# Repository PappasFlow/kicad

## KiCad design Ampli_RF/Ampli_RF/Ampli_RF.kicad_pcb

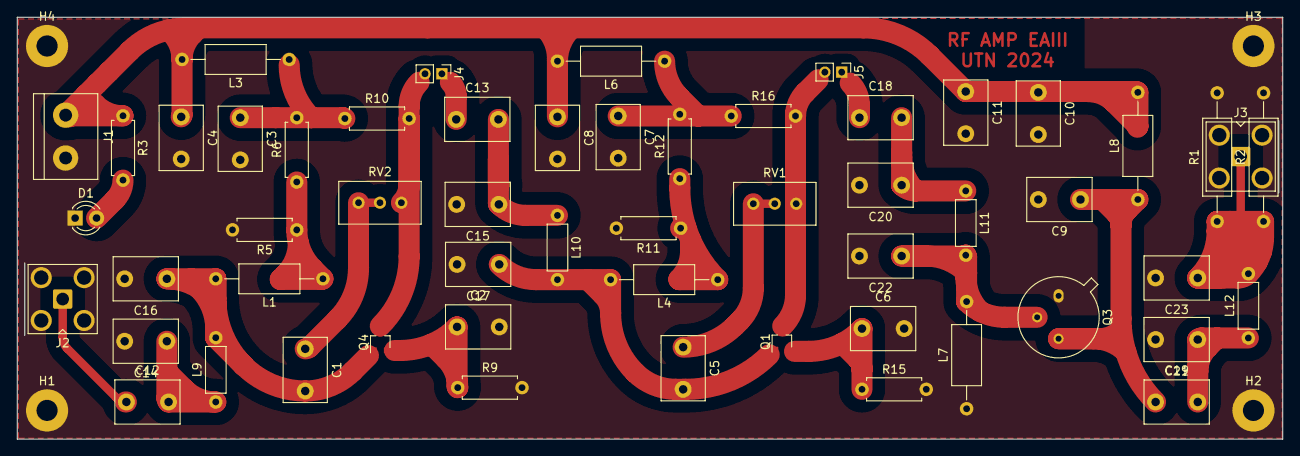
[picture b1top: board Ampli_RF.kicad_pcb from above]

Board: 2 copper layers, 150.0 x 50.0 mm, 59 parts (0 on the bottom side), 25 nets.

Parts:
C1, C2, C3, C4, C5, C6, C7, C8, C9, C10, C11, C12, C13, C14, C15, C16, C17, C18, C19, C20, C21, C22, C23: C; C_Disc_D7.5mm_W5.0mm_P5.00mm
D1: LED; LED_D3.0mm
H1, H2, H3, H4: MountingHole_Pad; MountingHole_2.5mm_Pad
J1: Con_power; TerminalBlock_bornier-2_P5.08mm
J2, J3: Con_signal; SMA_Amphenol_901-143_Horizontal
J4: E1; PinHeader_1x02_P2.00mm_Vertical
J5: E2; PinHeader_1x02_P2.00mm_Vertical
L1, L3, L4, L6, L7, L8: L; L_Axial_L7.0mm_D3.3mm_P12.70mm_Horizontal_Fastron_MICC
L9, L10, L11, L12: L; L_Axial_L5.3mm_D2.2mm_P7.62mm_Horizontal_Vishay_IM-1
Q1: BFR106; SOT-323_SC-70
Q3: 2N2219; TO-39-3
Q4: BFR182; SOT-323_SC-70
R1, R2: R; R_Axial_DIN0309_L9.0mm_D3.2mm_P15.24mm_Horizontal
R3, R5, R6, R9, R10, R11, R12, R15, R16: R; R_Axial_DIN0207_L6.3mm_D2.5mm_P7.62mm_Horizontal
RV1, RV2: pot; Potentiometer_Bourns_3296W_Vertical

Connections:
2N3866_in: C22.1, L7.2, L11.2, Q3.2 (B)
2N3866_out: C9.1, C19.1, L8.1, Q3.3 (C)
+12V: C4.1, C8.1, C10.1, C11.1, J1.1, L3.2, L6.2, L8.2, R3.1
BFR106_in: C5.2, C17.1, L4.2, L10.2, Q1.1 (B)
BFR106_out: J5.2, Q1.3 (C), R16.2, RV1.1
BFR182_in: C1.2, C16.1, L1.2, L9.2, Q4.1 (B)
BFR182_out: J4.2, Q4.3 (C), R10.2, RV2.1
GND: C2.2, C3.2, C4.2, C6.2, C7.2, C8.2, C9.2, C10.2, C11.2, C14.2, C15.2, C16.2, C17.2, C20.2, C21.2, C22.2, C23.2, D1.1 (K), H1.1, H2.1, H3.1, H4.1, J1.2, J2.2, J3.2, L7.1, Q3.1 (E), R1.2, R2.2, R5.2, R9.2, R11.2, R15.2
unnamed: C1.1, RV2.2, RV2.3
unnamed: C3.1, L3.1, R6.2, R10.1
unnamed: C5.1, RV1.2, RV1.3
unnamed: C7.1, L6.1, R12.2, R16.1
unnamed: C12.2, C14.1, L9.1
unnamed: C13.2, C15.1, L10.1
unnamed: C18.2, C20.1, L11.1
unnamed: C19.2, C21.1, L12.1
unnamed: D1.2 (A), R3.2
unnamed: C13.1, J4.1
unnamed: C18.1, J5.1
unnamed: L1.1, R5.1, R6.1
unnamed: L4.1, R11.1, R12.1
unnamed: C6.1, Q1.2 (E), R15.1
unnamed: C2.1, Q4.2 (E), R9.1
Output: C23.1, J3.1, L12.2, R1.1, R2.1
input: C12.1, J2.1

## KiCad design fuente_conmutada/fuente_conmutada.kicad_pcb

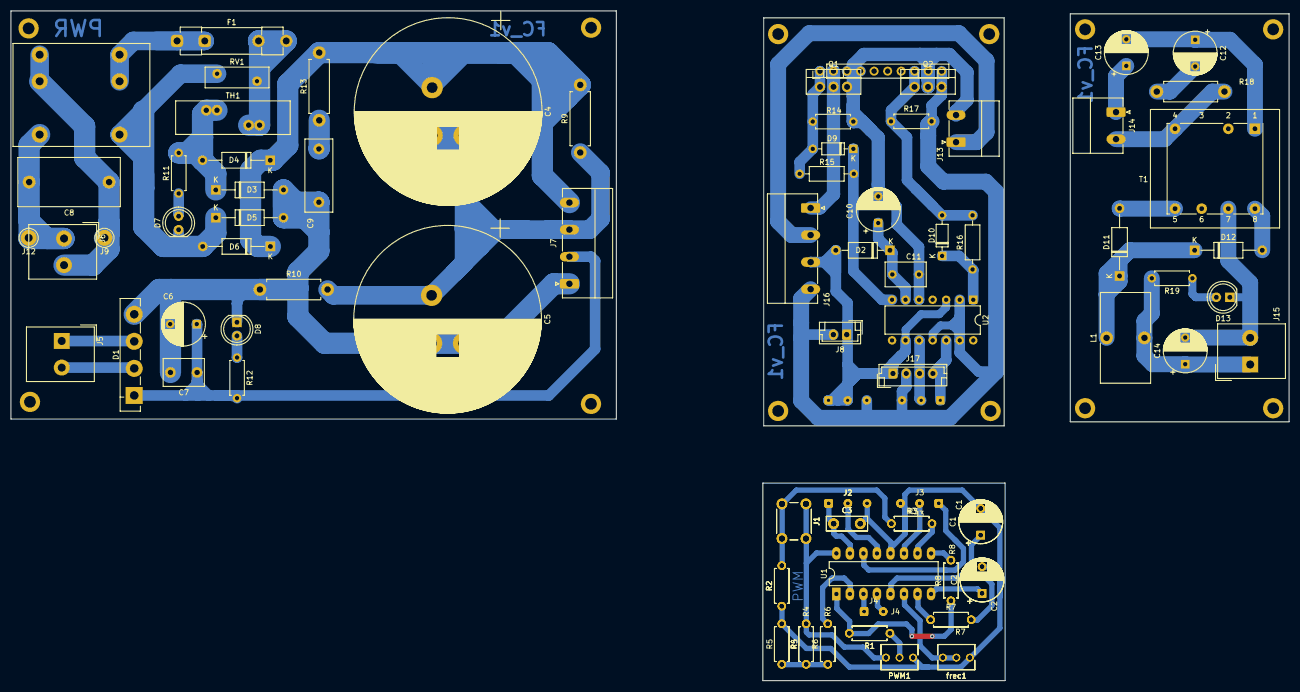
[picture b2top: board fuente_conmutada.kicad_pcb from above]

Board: 2 copper layers, 239.9 x 125.7 mm, 105 parts (0 on the bottom side), 46 nets.

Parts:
C1, C1#2: 1nF; CP_Radial_D8.0mm_P5.00mm
C2, C2#2: 10uF; CP_Radial_D8.0mm_P5.00mm
C3, C3#2: 0.1uF; C_Disc_D7.5mm_W2.5mm_P5.00mm
C4, C5: 470u; CP_Radial_D35.0mm_P9mm
C6: 1000uF; CP_Radial_D8.0mm_P5.00mm
C7: 100nF; C_Disc_D7.5mm_W5.0mm_P5.00mm
C8: 47n; C_Rect_L19.0mm_W9.0mm_P15.00mm_MKS4
C9: 10n; C_Rect_L13.5mm_W5.0mm_P10.00mm_FKS3_FKP3_MKS4
C10, C12, C13, C14: 100n; CP_Radial_D8.0mm_P5.00mm
C11: 22u; C_Disc_D7.5mm_W4.4mm_P5.00mm
D1: D_Bridge_+-AA; Diode_Bridge_Vishay_GBL
D2: D; D_A-405_P10.16mm_Horizontal
D3, D4, D5, D6, D11, D12: D; D_A-405_P12.70mm_Horizontal
D7, D8, D13: LED; LED_D5.0mm
D9, D10: 1N4148; D_DO-35_SOD27_P7.62mm_Horizontal
F1: Fuse; Fuseholder_Clip-5x20mm_Littelfuse_445-030_Inline_P20.50x5.2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
FL1: Filter_EMI; L_CommonMode_Toroid_filter_emi
H1, H2, H3, H4, H5, H6, H7, H8, H9, H10, H11, H12: MountingHole; MountingHole_2.2mm_M2_DIN965_Pad
J1, J1#2: shutdown; SW_PUSH_6mm_H9.5mm
J2, J2#2, J3, J3#2: Conn_01x03; SolderWire-0.1sqmm_1x03_P3.6mm_D0.4mm_OD1mm
J4, J4#2: Conn_01x02; SolderWire-0.1sqmm_1x02_P3.6mm_D0.4mm_OD1mm
J5: 12v _in; Altech_AK300_1x02_P5.00mm_45-Degree
J6: in_red; Altech_AK300_1x02_P5.00mm_45-Degree
J7: out_pwr; PhoenixContact_MC_1,5_4-G-5.08_1x04_P5.08mm_Horizontal
J8: fan; JST_EH_B2B-EH-A_1x02_P2.50mm_Vertical
J9, J12: pin; Pin_D1.3mm_L11.0mm_LooseFit
J10: pwm_power; SolderWire-0.1sqmm_1x03_P3.6mm_D0.4mm_OD1mm
J11: pwm_señal; SolderWire-0.1sqmm_1x03_P3.6mm_D0.4mm_OD1mm
J13: trafo; PhoenixContact_MC_1,5_2-G-5.08_1x02_P5.08mm_Horizontal
J14: in_trafo; PhoenixContact_MC_1,5_2-G-5.08_1x02_P5.08mm_Horizontal
J15: out_R; Altech_AK300_1x02_P5.00mm_45-Degree
J16: in_pwr; PhoenixContact_MC_1,5_4-G-5.08_1x04_P5.08mm_Horizontal
J17: in_pwr; JST_EH_B4B-EH-A_1x04_P2.50mm_Vertical
J19: montage; PinHeader_1x10_P2.54mm_Vertical
L1: L; L_Toroid_Vertical_L16.8mm_W9.2mm_P7.10mm_Vishay_TJ3
PWM1, PWM1#2: 10k; Potentiometer_Bourns_3266Y_Vertical
Q1, Q2: IRF740; TO-220-3_Vertical
R1, R1#2, R6, R6#2, R8, R8#2, R12: 1k; R_Axial_DIN0207_L6.3mm_D2.5mm_P7.62mm_Horizontal
R2, R2#2, R3, R3#2: 5k; R_Axial_DIN0207_L6.3mm_D2.5mm_P7.62mm_Horizontal
R4, R4#2, R5, R5#2, R14, R17: 10k; R_Axial_DIN0207_L6.3mm_D2.5mm_P7.62mm_Horizontal
R7, R7#2: 330; R_Axial_DIN0207_L6.3mm_D2.5mm_P7.62mm_Horizontal
R9, R10, R18: 150k; R_Axial_DIN0411_L9.9mm_D3.6mm_P12.70mm_Horizontal
R11, R19: 22k; R_Axial_DIN0207_L6.3mm_D2.5mm_P7.62mm_Horizontal
R13: 100; R_Axial_DIN0411_L9.9mm_D3.6mm_P12.70mm_Horizontal
R15, R16: 100; R_Axial_DIN0207_L6.3mm_D2.5mm_P10.16mm_Horizontal
RV1: Varistor; RV_Disc_D12mm_W3.9mm_P7.5mm
T1: Transformer_1P_SS; Transformer_Breve_TEZ-22x24
TH1: NTC; RV_Disc_D21.5mm_W6.3mm_P10mm
U1: UC3525; DIP-16_W7.62mm_LongPads
U2: IR2110; DIP-14_W7.62mm
frec1, frec1#2: 150k; Potentiometer_Bourns_3266Y_Vertical

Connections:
1a: D9.2 (A), J19.1, Q1.1 (G), R14.1, R15.2
1b: D10.2 (A), J19.8, Q2.1 (G), R16.2, R17.1
155V: C4.2, C5.1, J7.3, J13.1, J14.2, J16.2, R9.1, R10.2, R18.1, T1.2 (AB)
310V: C4.1, D4.1 (K), D6.1 (K), J7.4, J16.1, J19.2, Q1.2 (D), R9.2, R13.2
+12V: C3.1, J2.1
Fase: D3.1 (K), D4.2 (A), R11.2, TH1.2
GND: C1.2, C1#2.2, C2.2, C2#2.2, C3.2, C3#2.2, C5.2, C6.2, C7.2, C9.2, D1.4 (-), D3.2 (A), D5.2 (A), D8.1 (K), J2.3, J2#2.3, J3.3, J3#2.3, J7.1, J8.2, J10.3, J11.3, J16.4, J17.2, J19.10, PWM1.3, PWM1#2.3, Q2.3 (S), R2.1, R2#2.1, R5.1, R5#2.1, R10.1, R17.2, U1.12 (GND), U2.2 (COM), U2.11 (SD), U2.13 (VSS), frec1.3, frec1#2.3
GNDREF: C14.2, D13.1 (K), J15.2, T1.4 (SC)
HO: D9.1 (K), R15.1, U2.7 (HO)
LO: D10.1 (K), R16.1, U2.1 (LO)
unnamed: C9.1, R13.1
unnamed: C12.2, R18.2
unnamed: C10.1, C11.1, D2.1 (K), U2.6 (VB)
unnamed: D7.2 (A), R11.1
unnamed: D8.2 (A), R12.1
unnamed: D11.2 (A), T1.5 (SB)
unnamed: D11.1 (K), D12.1 (K), L1.1
unnamed: D12.2 (A), T1.3 (SA)
unnamed: D13.2 (A), R19.1
unnamed: F1.1, FL1.2
unnamed: F1.2, RV1.1, TH1.1
unnamed: J1.2, J1#2.2, R2.2, R2#2.2, R3.1, R3#2.1
unnamed: D1.3, J5.1
unnamed: D1.2, J5.2
unnamed: C8.1, FL1.1, J6.2, J9.1
unnamed: C8.2, FL1.3, J6.1, J12.1
unnamed: C14.1, J15.1, L1.2, R19.2
unnamed: PWM1.2, PWM1#2.2, R1.1, R1#2.1
unnamed: R4.1, R4#2.1, R5.2, R5#2.2, R6.1, R6#2.1
unnamed: C12.1, C13.2, T1.1 (AA)
unnamed: R8.2, R8#2.2, U1.9 (COMP)
unnamed: C1.1, C1#2.1, R7.2, R7#2.2, U1.5 (CT)
unnamed: R7.1, R7#2.1, U1.7 (DISCH)
unnamed: R1.2, R1#2.2, R8.1, R8#2.1, U1.1 (INV)
unnamed: R6.2, R6#2.2, U1.2 (NI)
unnamed: U1.6 (RT), frec1.1, frec1.2, frec1#2.1, frec1#2.2
unnamed: R3.2, R3#2.2, U1.10 (SD)
unnamed: C2.1, C2#2.1, U1.8 (SS)
Neutro: D5.1 (K), D6.2 (A), D7.1 (K), FL1.4, RV1.2
Osc: J4.2, J4#2.2, U1.4 (OSC)
OutA: J3.2, J3#2.2, J11.2, J17.3, U1.11 (OUTA), U2.10 (HIN)
OutB: J3.1, J3#2.1, J11.1, J17.4, U1.14 (OUTB), U2.12 (LIN)
Sync: J4.1, J4#2.1, U1.3 (SYNC)
VS: C10.2, C11.2, C13.1, J13.2, J14.1, J19.3, J19.4, J19.9, Q1.3 (S), Q2.2 (D), R14.2, U2.5 (VS)
Vc: C3#2.1, C6.1, C7.1, D1.1 (+), D2.2 (A), J2.2, J2#2.1, J2#2.2, J7.2, J8.1, J10.1, J10.2, J16.3, J17.1, R12.2, U1.13 (VC), U1.15 (VIN), U2.3 (VCC), U2.9 (VDD)
Vref: J1.1, J1#2.1, PWM1.1, PWM1#2.1, R4.2, R4#2.2, U1.16 (REF)

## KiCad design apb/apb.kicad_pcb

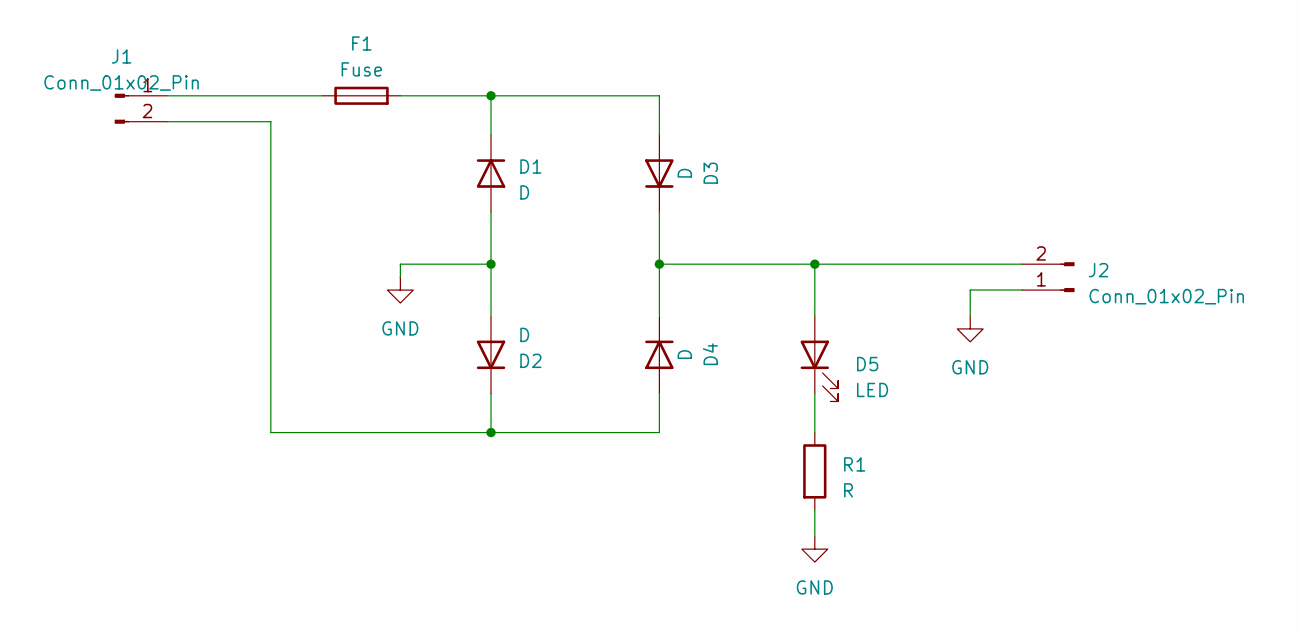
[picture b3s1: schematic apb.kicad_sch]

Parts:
D1, D2, D3, D4: D; D_5W_P10.16mm_Horizontal
D5: LED; LED_D3.0mm
F1: Fuse; Fuse_Blade_ATO_directSolder
J1, J2: Conn_01x02_Pin; Altech_AK300_1x02_P5.00mm_45-Degree
R1: R; R_Axial_DIN0411_L9.9mm_D3.6mm_P15.24mm_Horizontal

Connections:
GND: D1.2 (A), D2.2 (A), J2.1, R1.2
unnamed: D1.1 (K), D3.2 (A), F1.2
unnamed: D2.1 (K), D4.2 (A), J1.2
unnamed: D3.1 (K), D4.1 (K), D5.2 (A), J2.2
unnamed: D5.1 (K), R1.1
unnamed: F1.1, J1.1

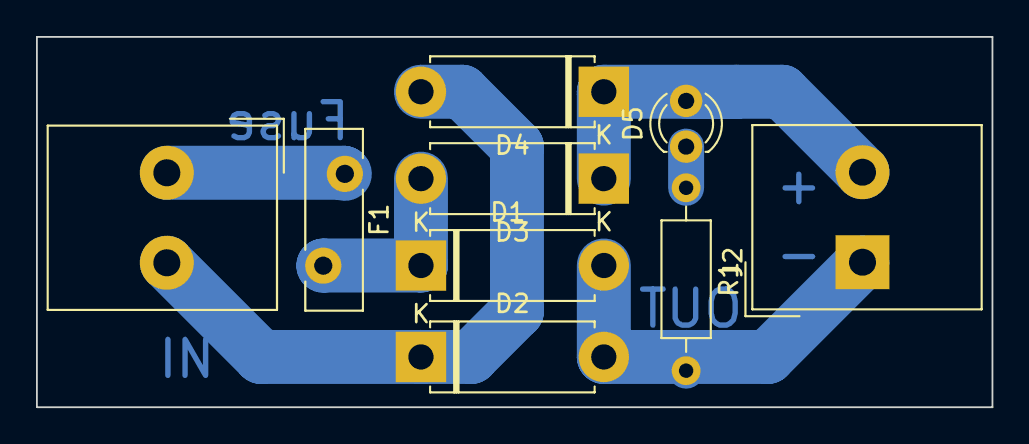
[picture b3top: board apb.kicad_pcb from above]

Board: 2 copper layers, 53.1 x 20.6 mm, 9 parts (0 on the bottom side), 6 nets.

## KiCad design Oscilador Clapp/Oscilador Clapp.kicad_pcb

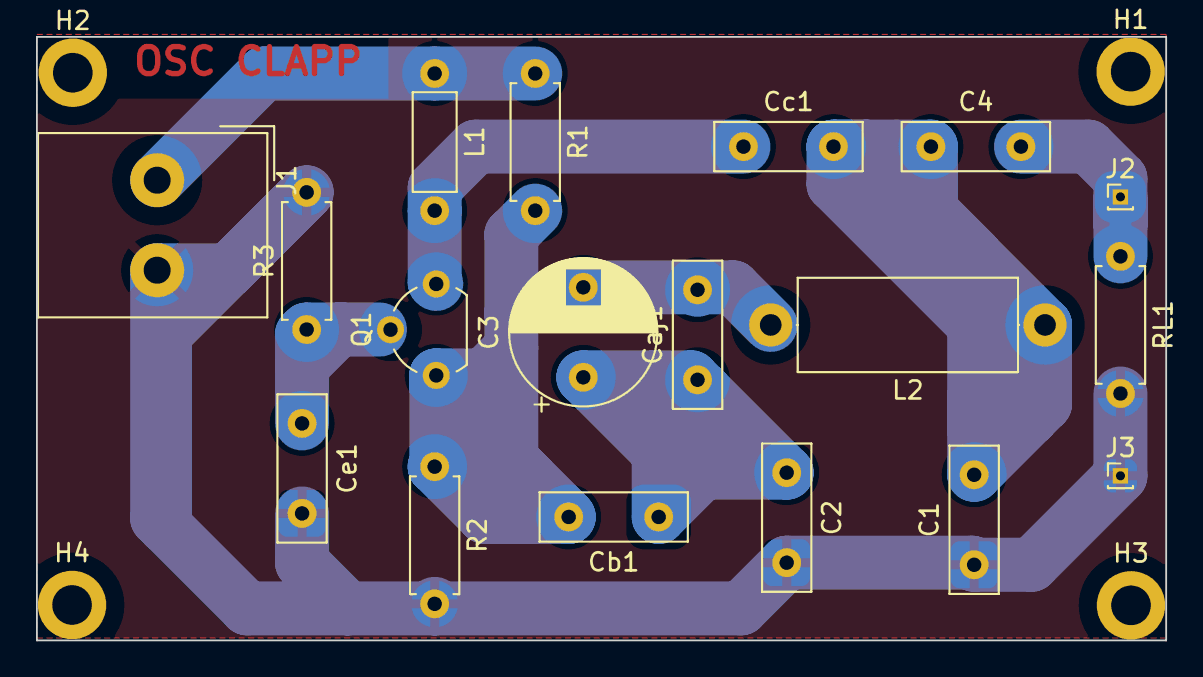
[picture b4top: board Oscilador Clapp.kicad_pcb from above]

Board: 2 copper layers, 62.7 x 33.5 mm, 22 parts (0 on the bottom side), 9 nets.

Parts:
C1, C2, C4: C; C_Disc_D8.0mm_W2.5mm_P5.00mm
C3: C; CP_Radial_D8.0mm_P5.00mm
Caj1: C; C_Disc_D8.0mm_W2.5mm_P5.00mm
Cb1: C; C_Disc_D8.0mm_W2.5mm_P5.00mm
Cc1: Cc; C_Disc_D8.0mm_W2.5mm_P5.00mm
Ce1: C; C_Disc_D8.0mm_W2.5mm_P5.00mm
H1, H2, H3, H4: MountingHole; MountingHole_2.2mm_M2_DIN965_Pad
J1: Conn_01x02; Altech_AK300_1x02_P5.00mm_45-Degree
J2, J3: Conn_01x01_Pin; PinHeader_1x01_P1.00mm_Vertical
L1: L; L_Axial_L5.3mm_D2.2mm_P7.62mm_Horizontal_Vishay_IM-1
L2: L; L_Axial_L12.0mm_D5.0mm_P15.24mm_Horizontal_Fastron_MISC
Q1: MPSH10; TO-92L_Wide
R1, R2, R3: R; R_Axial_DIN0207_L6.3mm_D2.5mm_P7.62mm_Horizontal
RL1: R; R_Axial_DIN0207_L6.3mm_D2.5mm_P7.62mm_Horizontal

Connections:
GND: C1.1, C2.2, Ce1.2, J1.2, J3.1, R2.2, R3.2, RL1.2
unnamed: C1.2, C4.1, Cc1.2, L2.1
unnamed: C2.1, C3.1, Caj1.1, Cb1.1
unnamed: C3.2, Caj1.2, L2.2
unnamed: C4.2, J2.1, RL1.1
unnamed: Cb1.2, R1.2, R2.1
unnamed: Cc1.1, L1.2, Q1.3 (C)
unnamed: Ce1.1, Q1.2 (E), R3.1
VCC: J1.1, L1.1, R1.1

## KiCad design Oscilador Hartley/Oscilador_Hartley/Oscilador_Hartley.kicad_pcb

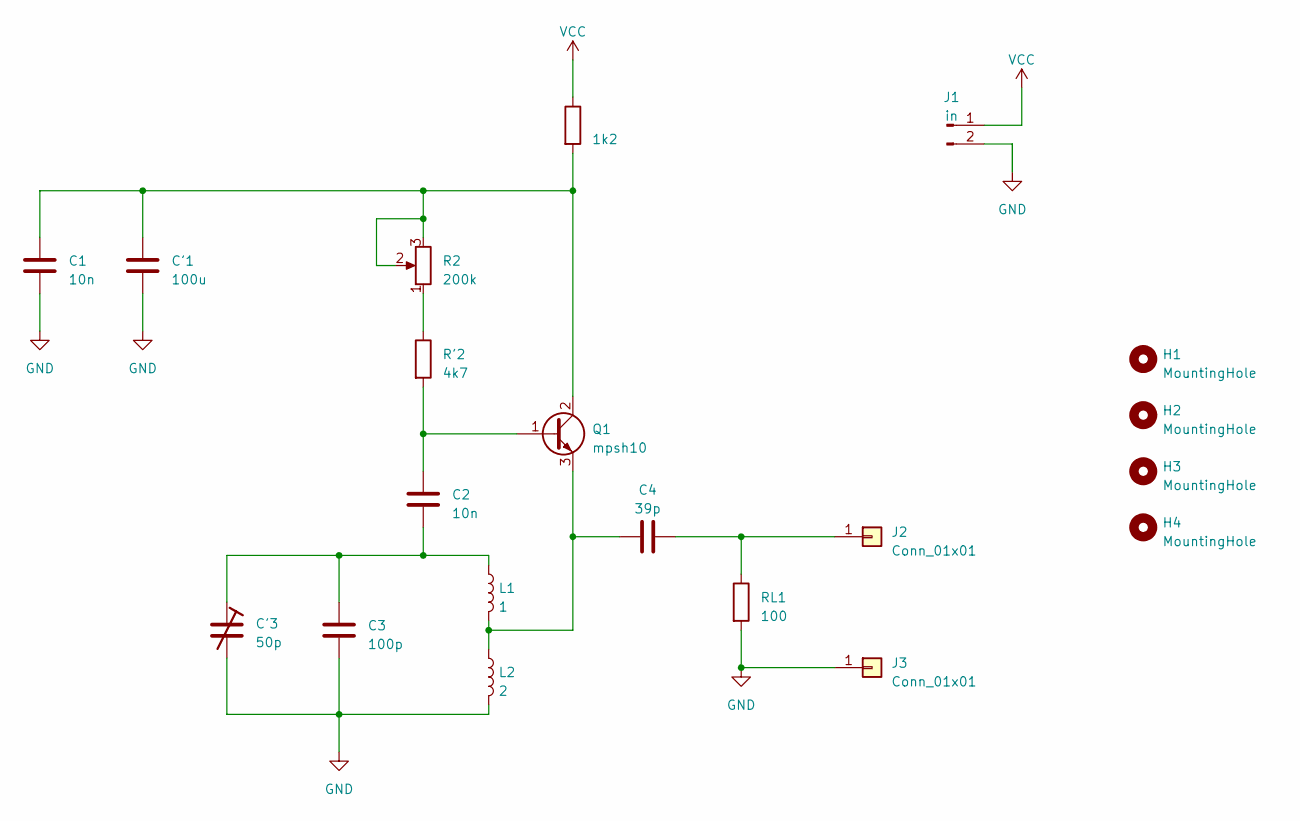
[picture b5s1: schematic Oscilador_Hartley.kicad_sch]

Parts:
C1: 10n; CP_Radial_D8.0mm_P5.00mm
C2: 10n; C_Disc_D7.5mm_W2.5mm_P5.00mm
C3: 100p; C_Disc_D7.5mm_W2.5mm_P5.00mm
C4: 39p; C_Disc_D7.5mm_W2.5mm_P5.00mm
C'1: 100u; C_Disc_D7.5mm_W2.5mm_P5.00mm
C'3: 50p; CP_Radial_D8.0mm_P5.00mm
H1, H2, H3, H4: MountingHole; MountingHole_2.2mm_M2_DIN965_Pad
J1: in; Altech_AK300_1x02_P5.00mm_45-Degree
J2, J3: Conn_01x01; PinHeader_1x01_P1.00mm_Vertical
L1: 1; L_Axial_L7.0mm_D3.3mm_P5.08mm_Vertical_Fastron_MICC
L2: 2; L_Axial_L9.5mm_D4.0mm_P15.24mm_Horizontal_Fastron_SMCC
Q1: mpsh10; TO-92L_Wide
R1: 1k2; R_Axial_DIN0207_L6.3mm_D2.5mm_P7.62mm_Horizontal
R2: 200k; Potentiometer_Bourns_3266Y_Vertical
R'2: 4k7; R_Axial_DIN0207_L6.3mm_D2.5mm_P7.62mm_Horizontal
RL1: 100; R_Axial_DIN0207_L6.3mm_D2.5mm_P7.62mm_Horizontal

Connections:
GND: C1.2, C3.2, C'1.2, C'3.2, J1.2, J3.1, L2.2, RL1.2
unnamed: C2.2, C3.1, C'3.1, L1.1
unnamed: C4.2, J2.1, RL1.1
unnamed: C2.1, Q1.1 (B), R'2.2
unnamed: C1.1, C'1.1, Q1.2 (C), R1.2, R2.2, R2.3
unnamed: C4.1, L1.2, L2.1, Q1.3 (E)
unnamed: R2.1, R'2.1
VCC: J1.1, R1.1

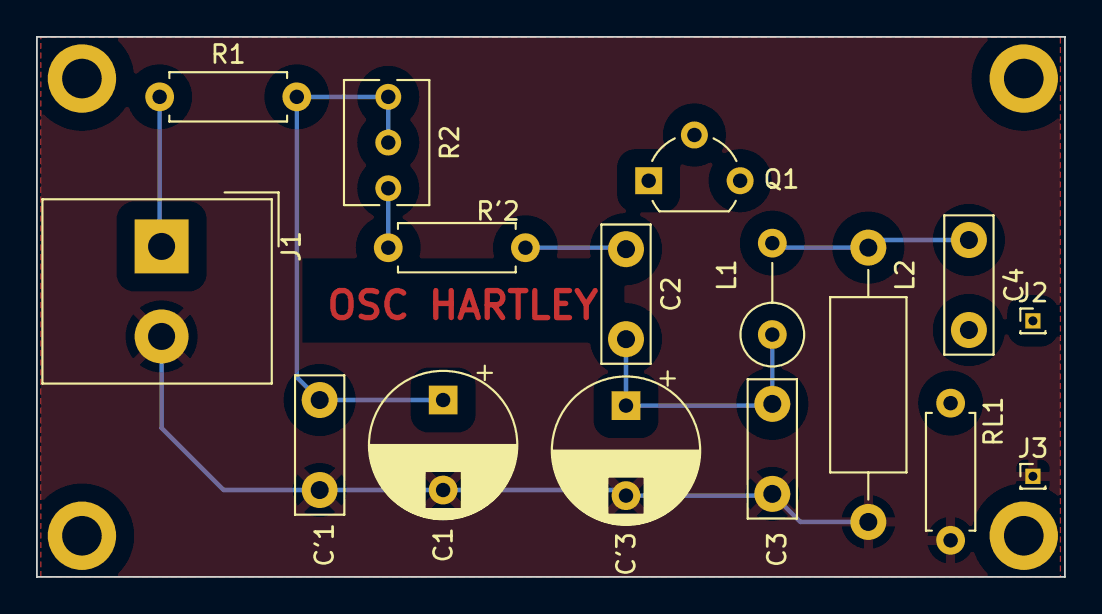
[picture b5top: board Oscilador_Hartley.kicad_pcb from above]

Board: 2 copper layers, 57.1 x 30.0 mm, 20 parts (0 on the bottom side), 8 nets.

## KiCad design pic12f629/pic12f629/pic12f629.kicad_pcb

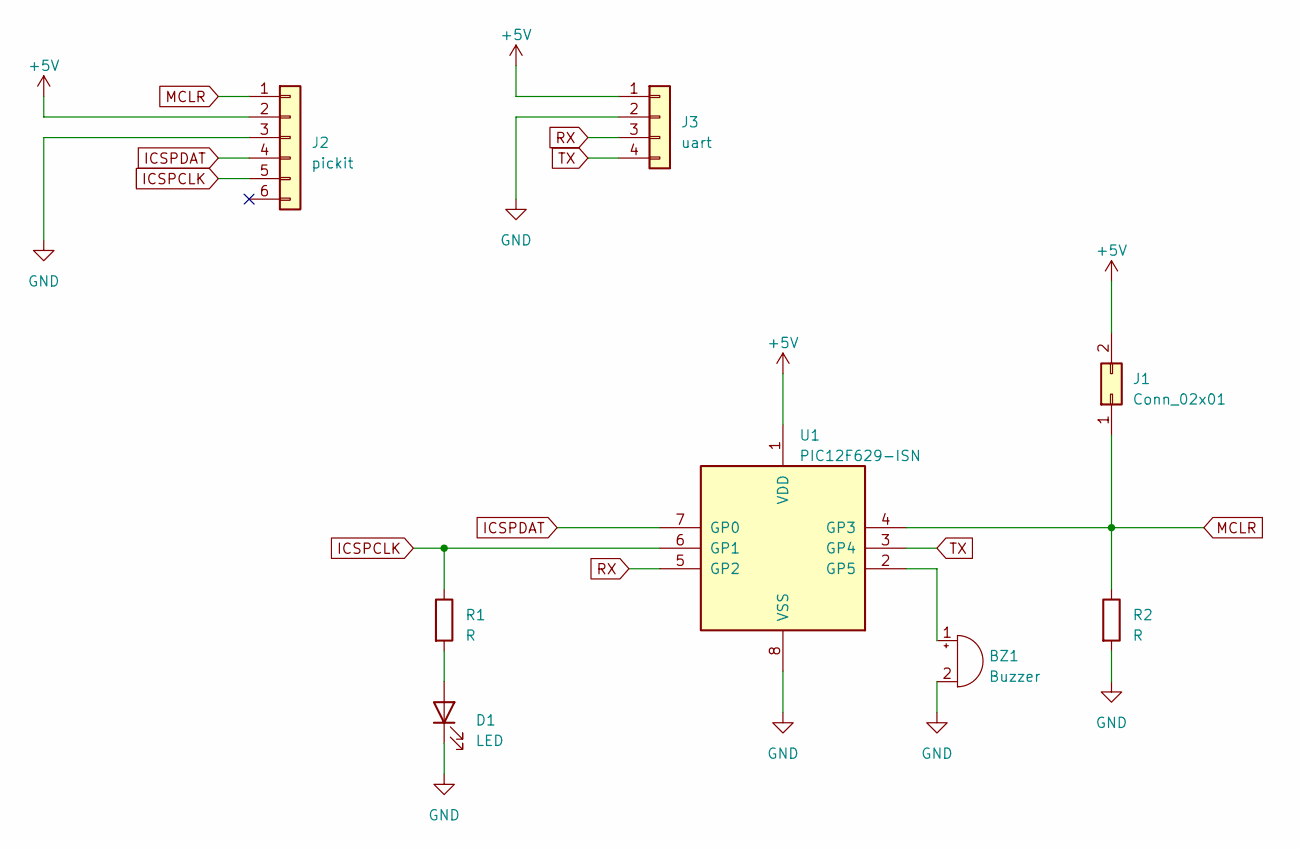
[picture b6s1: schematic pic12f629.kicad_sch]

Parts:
BZ1: Buzzer; MagneticBuzzer_Kingstate_KCG0601
D1: LED; LED_D5.0mm
J1: Conn_02x01; SW_PUSH-12mm
J2: pickit; PinHeader_1x06_P2.00mm_Horizontal
J3: uart; PinHeader_1x04_P2.00mm_Horizontal
R1, R2: R; R_Axial_DIN0207_L6.3mm_D2.5mm_P10.16mm_Horizontal
U1: PIC12F629-ISN; DIP-8_W7.62mm

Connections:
+5V: J1.2, J2.2, J3.1, U1.1 (VDD)
GND: BZ1.2 (+), D1.1 (K), J2.3, J3.2, R2.2, U1.8 (VSS)
ICSPCLK: J2.5, R1.1, U1.6 (GP1)
ICSPDAT: J2.4, U1.7 (GP0)
MCLR: J1.1, J2.1, R2.1, U1.4 (GP3)
unnamed: BZ1.1 (-), U1.2 (GP5)
unnamed: D1.2 (A), R1.2
RX: J3.3, U1.5 (GP2)
TX: J3.4, U1.3 (GP4)

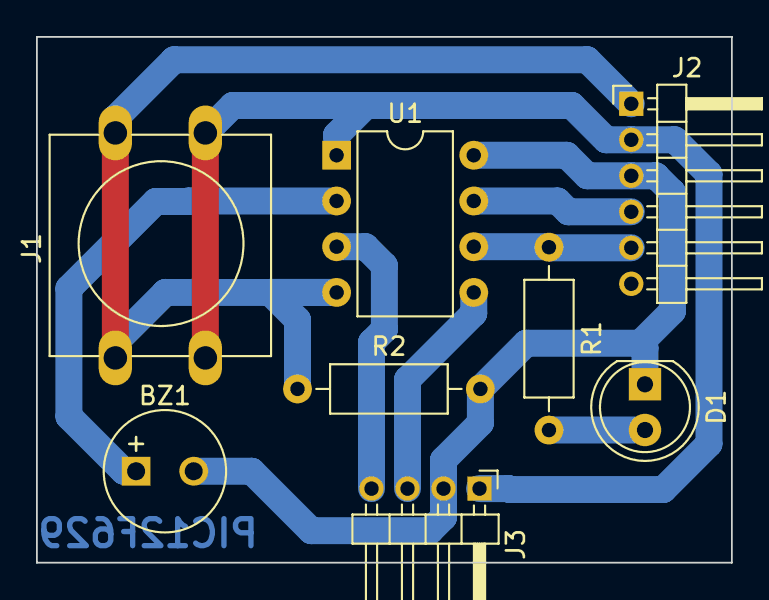
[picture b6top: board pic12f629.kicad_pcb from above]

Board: 2 copper layers, 38.6 x 29.2 mm, 8 parts (0 on the bottom side), 9 nets.

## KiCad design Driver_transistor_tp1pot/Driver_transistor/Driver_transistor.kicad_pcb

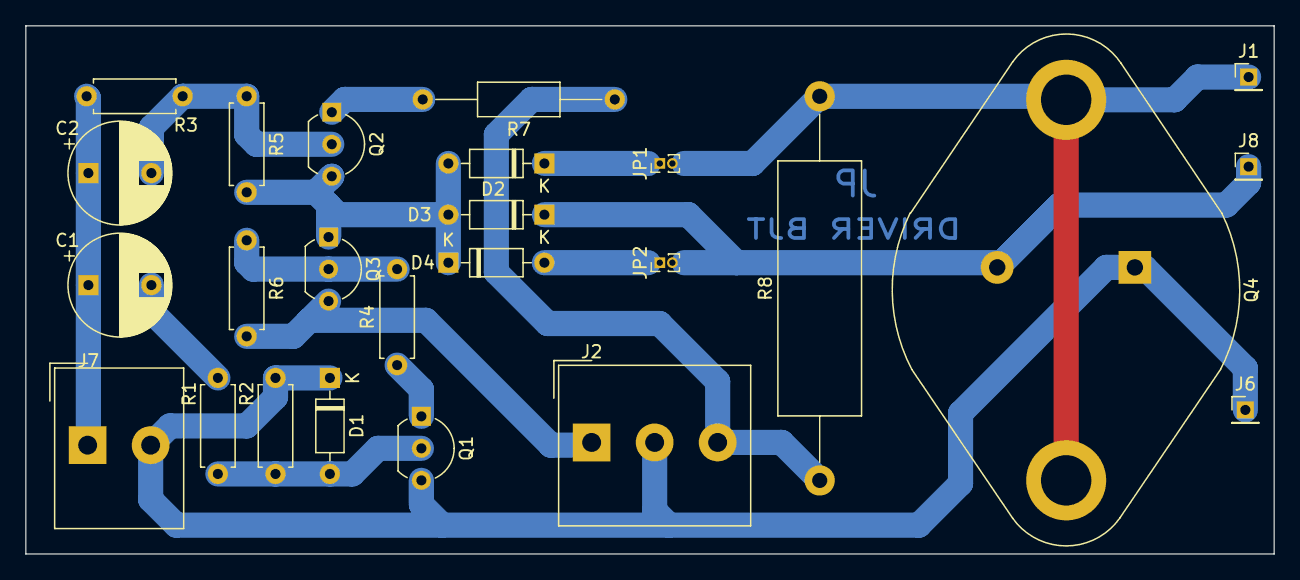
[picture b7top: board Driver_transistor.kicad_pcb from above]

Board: 2 copper layers, 99.1 x 41.9 mm, 25 parts (0 on the bottom side), 15 nets.

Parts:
C1: 10nF; CP_Radial_D8.0mm_P5.00mm
C2: 150pF; CP_Radial_D8.0mm_P5.00mm
D1, D2, D3, D4: 1N4148; D_DO-35_SOD27_P7.62mm_Horizontal
J1: colector; PinHeader_1x01_P2.00mm_Vertical
J2: Conn_01x03; Altech_AK300_1x03_P5.00mm_45-Degree
J6: emisor; PinHeader_1x01_P2.00mm_Vertical
J7: Conn_01x02; Altech_AK300_1x02_P5.00mm_45-Degree
J8: base; PinHeader_1x01_P2.00mm_Vertical
JP1, JP2: Jumper; PinHeader_1x02_P1.00mm_Vertical
Q1: BC557; TO-92_Inline_Wide
Q2, Q3: BC548; TO-92_Inline_Wide
Q4: BU208A; TO-3
R1: 270; R_Axial_DIN0207_L6.3mm_D2.5mm_P7.62mm_Horizontal
R2: 1k; R_Axial_DIN0207_L6.3mm_D2.5mm_P7.62mm_Horizontal
R3: 820; R_Axial_DIN0207_L6.3mm_D2.5mm_P7.62mm_Horizontal
R4: 150; R_Axial_DIN0207_L6.3mm_D2.5mm_P7.62mm_Horizontal
R5: 220; R_Axial_DIN0207_L6.3mm_D2.5mm_P7.62mm_Horizontal
R6: 100; R_Axial_DIN0207_L6.3mm_D2.5mm_P7.62mm_Horizontal
R7: 120; R_Axial_DIN0207_L6.3mm_D2.5mm_P15.24mm_Horizontal
R8: 12 ohm 7w; R_Axial_Power_L20.0mm_W6.4mm_P30.48mm

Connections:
+12V: J2.3, R7.1, R8.1
-12V: J2.1, Q3.3 (E), R6.2
GND: D1.1 (K), J2.2, J6.1, J7.2, Q1.3 (E), Q4.1 (E), R2.2
unnamed: C1.2, R1.1
unnamed: D1.2 (A), Q1.2 (B), R1.2, R2.1
unnamed: D2.2 (A), D3.2 (A), D4.1 (K), Q2.3 (E), Q3.1 (C), R5.2
unnamed: D2.1 (K), JP1.1 (A)
unnamed: D3.1 (K), J8.1, JP2.2 (B), Q4.2 (B)
unnamed: D4.2 (A), JP2.1 (A)
unnamed: Q1.1 (C), R4.1
unnamed: C2.2, Q2.2 (B), R3.2, R5.1
unnamed: Q2.1 (C), R7.2
unnamed: Q3.2 (B), R4.2, R6.1
colector: J1.1, JP1.2 (B), Q4.3 (C), R8.2
pwm: C1.1, C2.1, J7.1, R3.1

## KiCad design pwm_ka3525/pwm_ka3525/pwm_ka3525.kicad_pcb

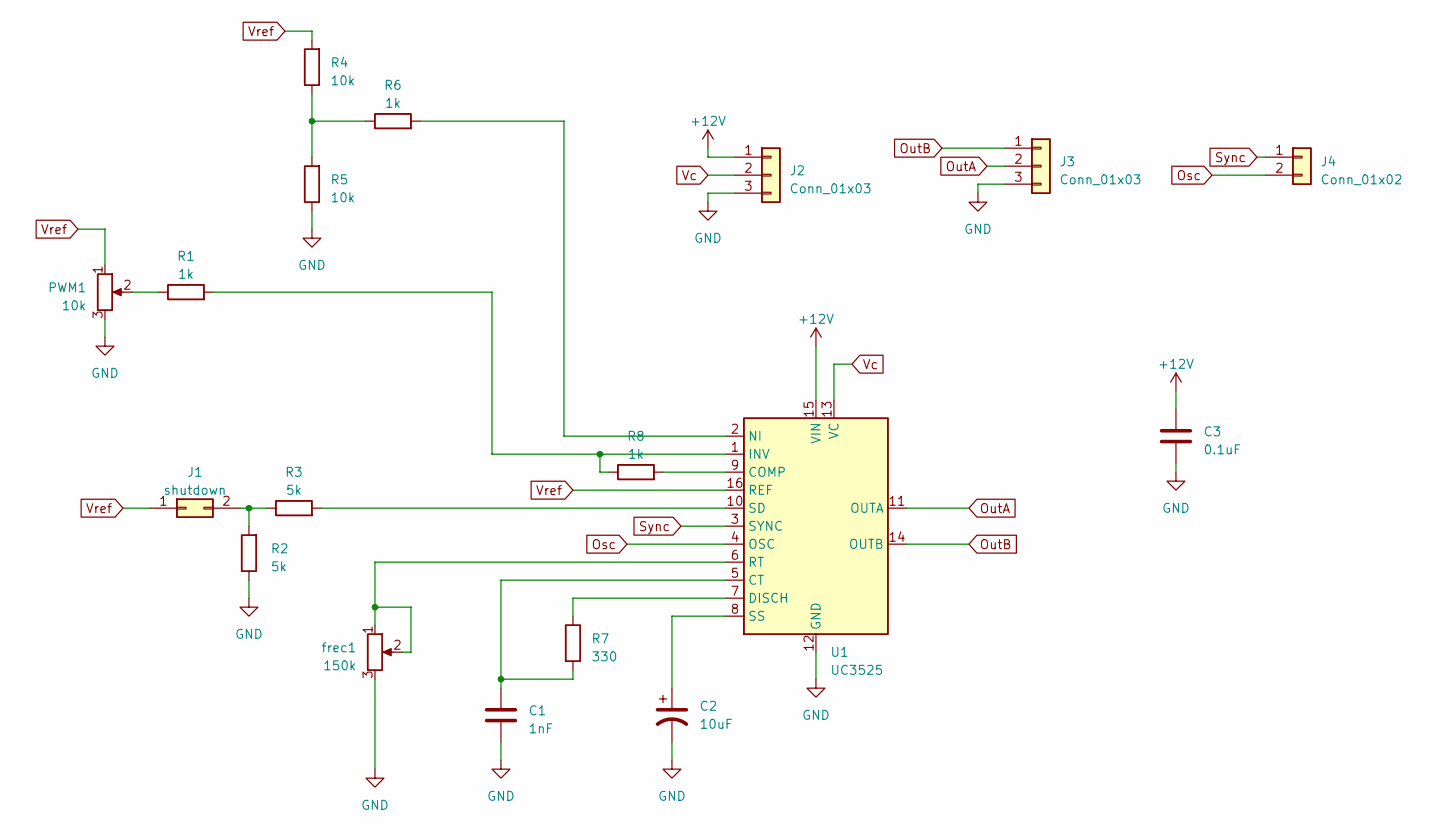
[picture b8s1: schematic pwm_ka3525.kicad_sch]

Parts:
C1: 1nF; CP_Radial_D8.0mm_P5.00mm
C2: 10uF; CP_Radial_D8.0mm_P5.00mm
C3: 0.1uF; C_Disc_D7.5mm_W2.5mm_P5.00mm
J1: shutdown; SW_PUSH_6mm_H9.5mm
J2, J3: Conn_01x03; SolderWire-0.1sqmm_1x03_P3.6mm_D0.4mm_OD1mm
J4: Conn_01x02; SolderWire-0.1sqmm_1x02_P3.6mm_D0.4mm_OD1mm
PWM1: 10k; Potentiometer_Bourns_3266Y_Vertical
R1, R6, R8: 1k; R_Axial_DIN0207_L6.3mm_D2.5mm_P7.62mm_Horizontal
R2, R3: 5k; R_Axial_DIN0207_L6.3mm_D2.5mm_P7.62mm_Horizontal
R4, R5: 10k; R_Axial_DIN0207_L6.3mm_D2.5mm_P7.62mm_Horizontal
R7: 330; R_Axial_DIN0207_L6.3mm_D2.5mm_P7.62mm_Horizontal
U1: UC3525; DIP-16_W7.62mm_LongPads
frec1: 150k; Potentiometer_Bourns_3266Y_Vertical

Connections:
+12V: C3.1, J2.1, U1.15 (VIN)
GND: C1.2, C2.2, C3.2, J2.3, J3.3, PWM1.3, R2.1, R5.1, U1.12 (GND), frec1.3
unnamed: J1.2, R2.2, R3.1
unnamed: PWM1.2, R1.1
unnamed: R4.1, R5.2, R6.1
unnamed: R8.2, U1.9 (COMP)
unnamed: C1.1, R7.2, U1.5 (CT)
unnamed: R7.1, U1.7 (DISCH)
unnamed: R1.2, R8.1, U1.1 (INV)
unnamed: R6.2, U1.2 (NI)
unnamed: U1.6 (RT), frec1.1, frec1.2
unnamed: R3.2, U1.10 (SD)
unnamed: C2.1, U1.8 (SS)
Osc: J4.2, U1.4 (OSC)
OutA: J3.2, U1.11 (OUTA)
OutB: J3.1, U1.14 (OUTB)
Sync: J4.1, U1.3 (SYNC)
Vc: J2.2, U1.13 (VC)
Vref: J1.1, PWM1.1, R4.2, U1.16 (REF)

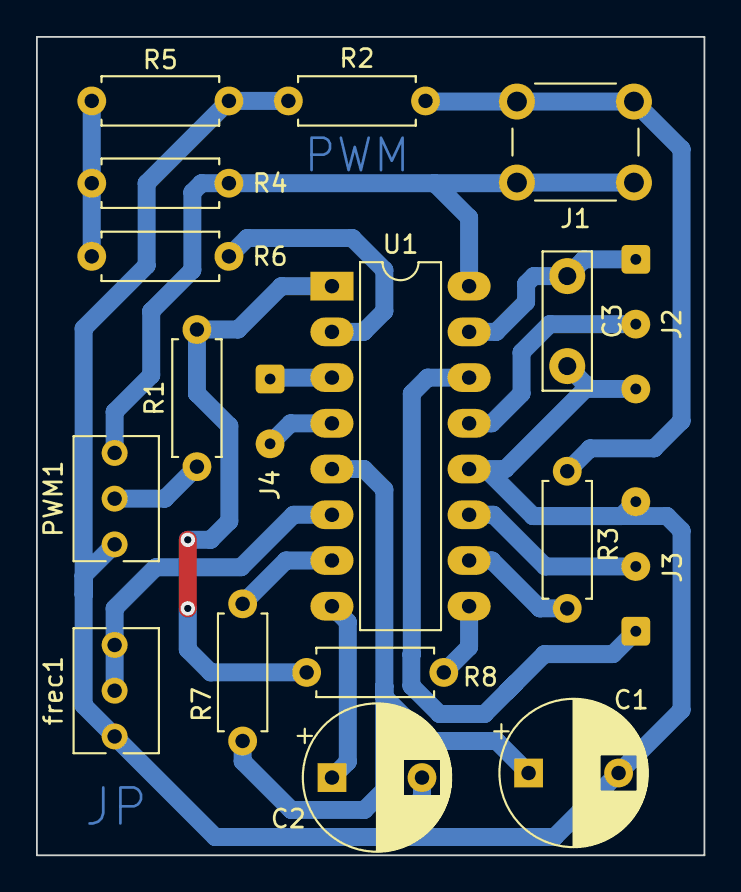
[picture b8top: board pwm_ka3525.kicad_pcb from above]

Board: 2 copper layers, 37.1 x 45.5 mm, 18 parts (0 on the bottom side), 19 nets.

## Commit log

2024-03-26 actualizacion
2024-03-30 potencia
2024-04-16 rediseño driver BJT
2024-04-16 rediseño driver IGBT-MOSFET
2024-04-17 para vos juan
2024-04-24 PIC12F629
2024-05-05 OscHartley
2024-06-08 fc_v1
2024-07-09 fc_v1(final)
2024-10-12 ampRF
